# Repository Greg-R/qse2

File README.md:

QSE2DCEZ Transmitter Module

The documentation for this design is located here:
<https://kf5n.com/t41-2/qse2dcez/>

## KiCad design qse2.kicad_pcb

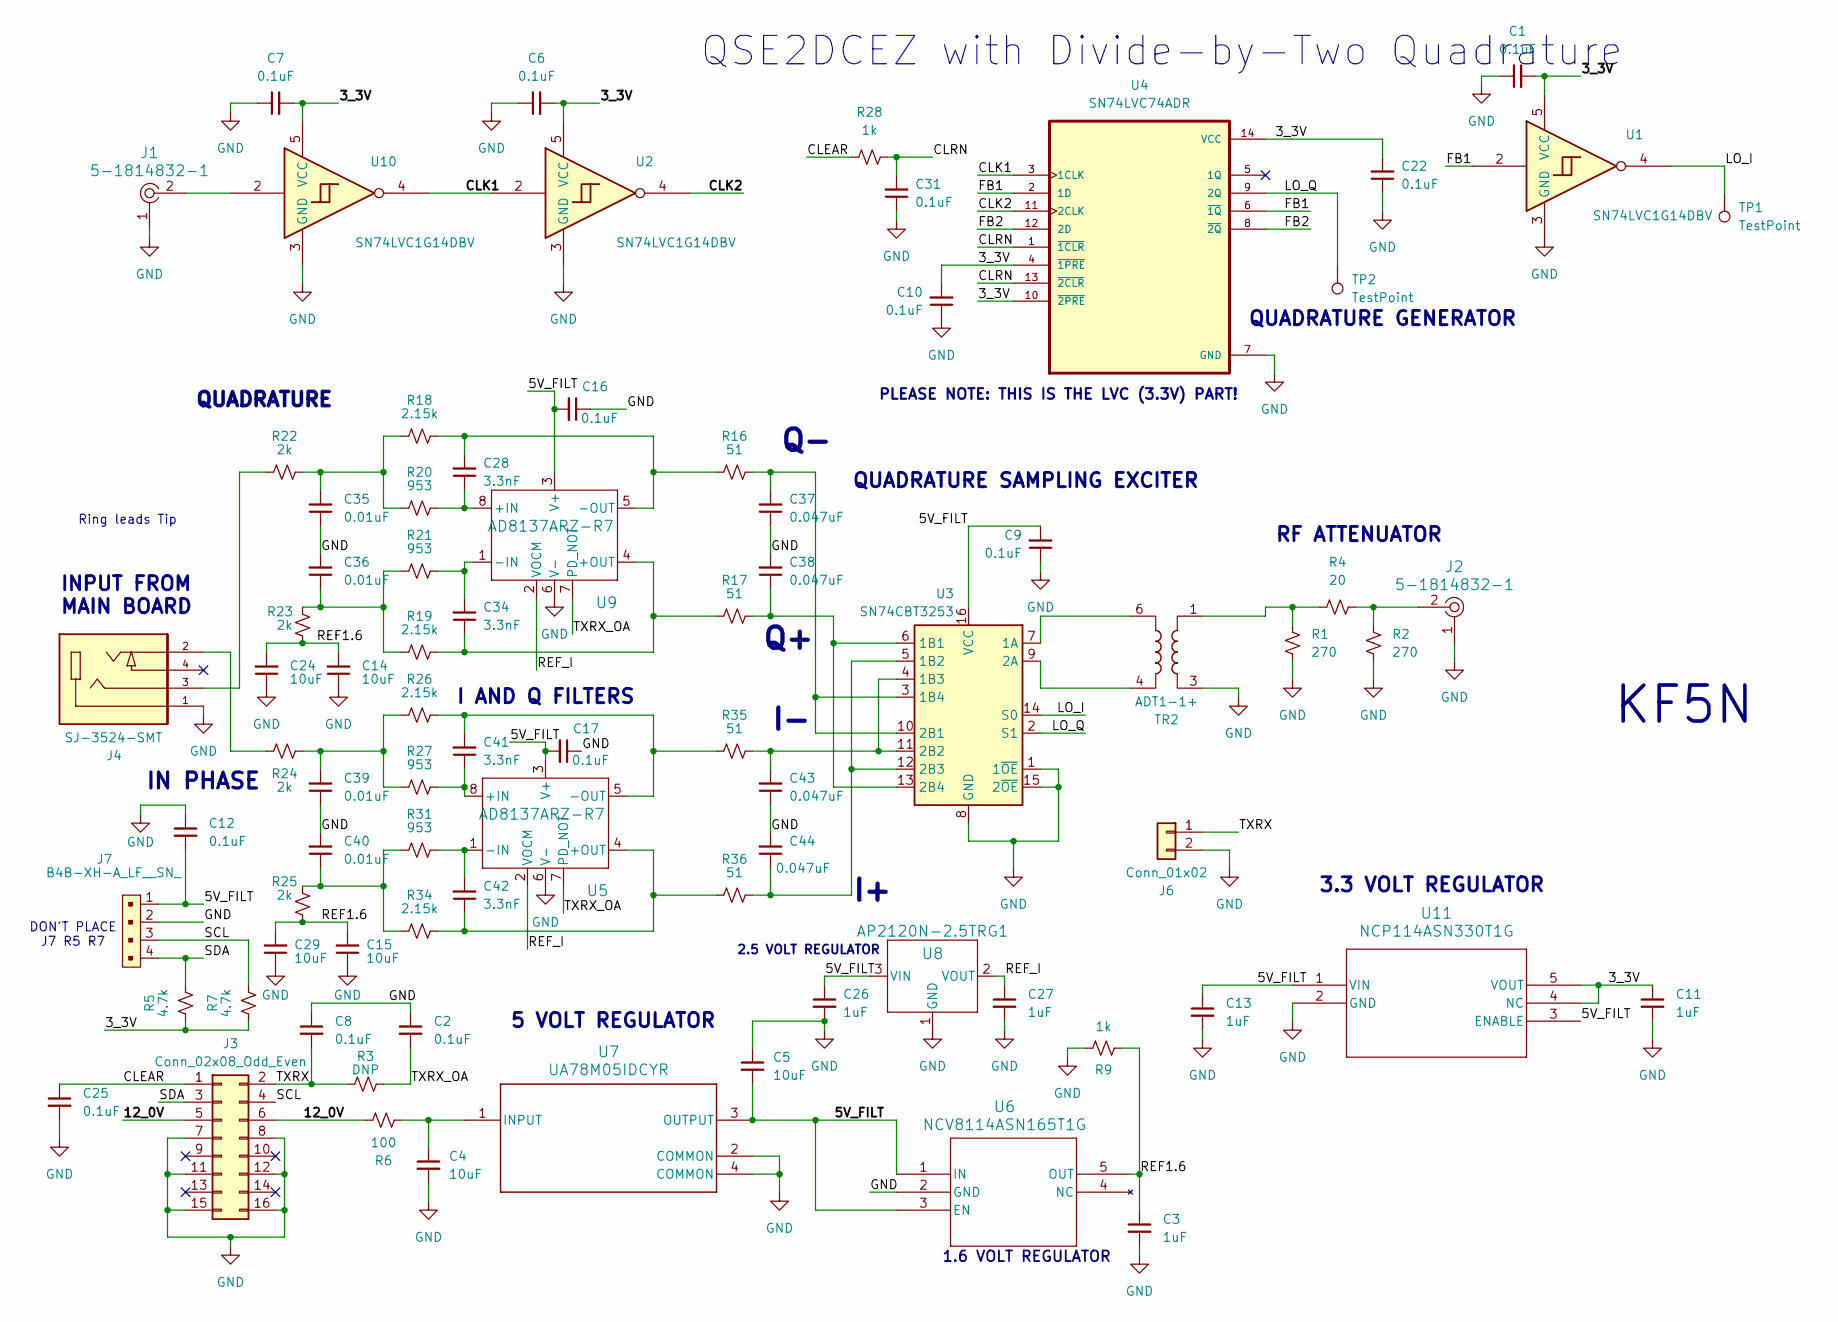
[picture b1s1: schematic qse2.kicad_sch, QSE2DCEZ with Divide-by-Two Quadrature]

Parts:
C1, C2, C6, C7, C8, C9, C10, C12, C16, C17, C22, C25, C31: 0.1uF; C_1206_3216Metric
C3, C11, C13, C26, C27: 1uF; C_1206_3216Metric
C4, C5, C14, C15, C24, C29: 10uF; C_1206_3216Metric
C28, C34, C41, C42: 3.3nF; C_1206_3216Metric
C35, C36, C39, C40: 0.01uF; C_1206_3216Metric
C37, C38, C43, C44: 0.047uF; C_1206_3216Metric
J1, J2: 5-1814832-1; RF_SMA_Vertical_5-1814832-1; MPN 5-1814832-1; Digi-Key_PN A97594-ND
J3: Conn_02x08_Odd_Even; IDC-Header_2x08_P2.54mm_Vertical
J4: SJ-3524-SMT; CUI_SJ-3524-SMT; PARTREV 1.03
J6: Conn_01x02; PinHeader_1x2_P2.5mm_Drill1.1mm
J7: B4B-XH-A_LF__SN_; PinHeader_1x4_P2.5mm_Drill1.1mm; MPN B4B-XH-A(LF)(SN); Digi-Key_PN 455-2249-ND
R1, R2: 270; R_1206_3216Metric
R3: DNP; R_1206_3216Metric
R4: 20; R_1206_3216Metric
R5, R7: 4.7k; R_1206_3216Metric
R6: 100; R_1206_3216Metric
R9, R28: 1k; R_1206_3216Metric
R16, R17, R35, R36: 51; R_1206_3216Metric
R18, R19, R26, R34: 2.15k; R_1206_3216Metric
R20, R21, R27, R31: 953; R_1206_3216Metric
R22, R23, R24, R25: 2k; R_1206_3216Metric
TP1, TP2: TestPoint; TestPoint_Pad_D1.0mm
TR2: ADT1-1+; Mini-Circuits_CD542_H2.84mm
U1, U2, U10: SN74LVC1G14DBV; SOT-23-5
U3: SN74CBT3253; SOIC-16_3.9x9.9mm_P1.27mm
U4: SN74LVC74ADR; SOIC-14_3.9x8.7mm_P1.27mm
U5, U9: AD8137ARZ-R7; R_8_ADI
U6: NCV8114ASN165T1G; TSOP-5-483-N_ONS
U7: UA78M05IDCYR; DCY0004A_N
U8: AP2120N-2.5TRG1; SOT-23_DIO
U11: NCP114ASN330T1G; TSOP-5-483-N_ONS

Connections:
/3_3V: C1.2, C6.2, C7.2, C10.2, C11.1, C22.2, R5.1, R7.1, U1.5 (VCC), U2.5 (VCC), U4.4 (~1PRE), U4.10 (~2PRE), U4.14 (VCC), U10.5 (VCC), U11.4 (NC), U11.5 (VOUT)
/5V_FILT: C5.2, C9.2, C12.2, C13.1, C16.2, C17.2, C26.1, J7.1, U3.16 (VCC), U5.3 (V+), U6.1 (IN), U6.3 (EN), U7.3 (OUTPUT), U8.3 (VIN), U9.3 (V+), U11.1 (VIN), U11.3 (ENABLE)
/12_0V: J3.5, J3.6, R6.1
/CLEAR: C25.1, J3.1, R28.1
/CLK1: U2.2, U4.3 (1CLK), U10.4
/CLK2: U2.4, U4.11 (2CLK)
/CLRN: C31.2, R28.2, U4.1 (~1CLR), U4.13 (~2CLR)
/FB1: U1.2, U4.2 (1D), U4.6 (~1Q)
/FB2: U4.8 (~2Q), U4.12 (2D)
/LO_I: TP1.1 (1_1), U1.4, U3.14 (S0)
/LO_Q: TP2.1 (1_1), U3.2 (S1), U4.9 (2Q)
/REF1.6: C3.1, C14.2, C15.2, C24.2, C29.2, R9.2, R23.1, R25.1, U6.5 (OUT)
/REF_I: C27.1, U5.2 (VOCM), U8.2 (VOUT), U9.2 (VOCM)
/SCL: J3.4, J7.3, R7.2
/SDA: J3.3, J7.4, R5.2
/TXRX: C8.2, J3.2, J6.1, R3.1
/TXRX_OA: C2.2, R3.2, U5.7 (PD_NOT), U9.7 (PD_NOT)
GND: C1.1, C2.1, C3.2, C4.2, C5.1, C6.1, C7.1, C8.1, C9.1, C10.1, C11.2, C12.1, C13.2, C14.1, C15.1, C16.1, C17.1, C22.1, C24.1, C25.2, C26.2, C27.2, C29.1, C31.1, C35.1, C36.2, C37.1, C38.2, C39.1, C40.2, C43.1, C44.2, J1.1, J2.1, J3.7, J3.8, J3.11, J3.12, J3.15, J3.16, J4.1, J6.2, J7.2, R1.2, R2.2, R9.1, TR2.3, U1.3 (GND), U2.3 (GND), U3.1 (1~OE), U3.8 (GND), U3.15 (2~OE), U4.7 (GND), U5.6 (V-), U6.2 (GND), U7.2 (COMMON), U7.4 (COMMON), U8.1 (GND), U9.6 (V-), U10.3 (GND), U11.2 (GND)
unnamed: C35.2, R18.1, R20.1, R22.2
unnamed: C36.1, R19.1, R21.1, R23.2
unnamed: C39.2, R24.2, R26.1, R27.1
unnamed: C40.1, R25.2, R31.1, R34.1
unnamed: J1.2, U10.2
unnamed: J2.2, R2.1, R4.2
unnamed: J4.2, R24.1
unnamed: J4.3, R22.1
unnamed: R1.1, R4.1, TR2.1
unnamed: TR2.6, U3.7 (1A)
unnamed: C38.1, R17.2, U3.6 (1B1), U3.13 (2B4)
unnamed: C44.1, R36.2, U3.5 (1B2), U3.12 (2B3)
unnamed: C43.2, R35.2, U3.4 (1B3), U3.11 (2B2)
unnamed: C37.2, R16.2, U3.3 (1B4), U3.10 (2B1)
unnamed: TR2.4, U3.9 (2A)
unnamed: C41.1, R27.2, U5.8 (+IN)
unnamed: C42.1, R34.2, R36.1, U5.4 (+OUT)
unnamed: C42.2, R31.2, U5.1 (-IN)
unnamed: C41.2, R26.2, R35.1, U5.5 (-OUT)
unnamed: C4.1, R6.2, U7.1 (INPUT)
unnamed: C28.1, R20.2, U9.8 (+IN)
unnamed: C34.1, R17.1, R19.2, U9.4 (+OUT)
unnamed: C34.2, R21.2, U9.1 (-IN)
unnamed: C28.2, R16.1, R18.2, U9.5 (-OUT)

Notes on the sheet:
Ring leads Tip
3.3 VOLT REGULATOR
KF5N
QUADRATURE
DON'T PLACE J7 R5 R7
IN PHASE
QUADRATURE SAMPLING EXCITER
QUADRATURE GENERATOR
1.6 VOLT REGULATOR
RF ATTENUATOR
PLEASE NOTE: THIS IS THE LVC (3.3V) PART!
INPUT FROM MAIN BOARD
I AND Q FILTERS
5 VOLT REGULATOR
QSE2DCEZ with Divide-by-Two Quadrature
2.5 VOLT REGULATOR

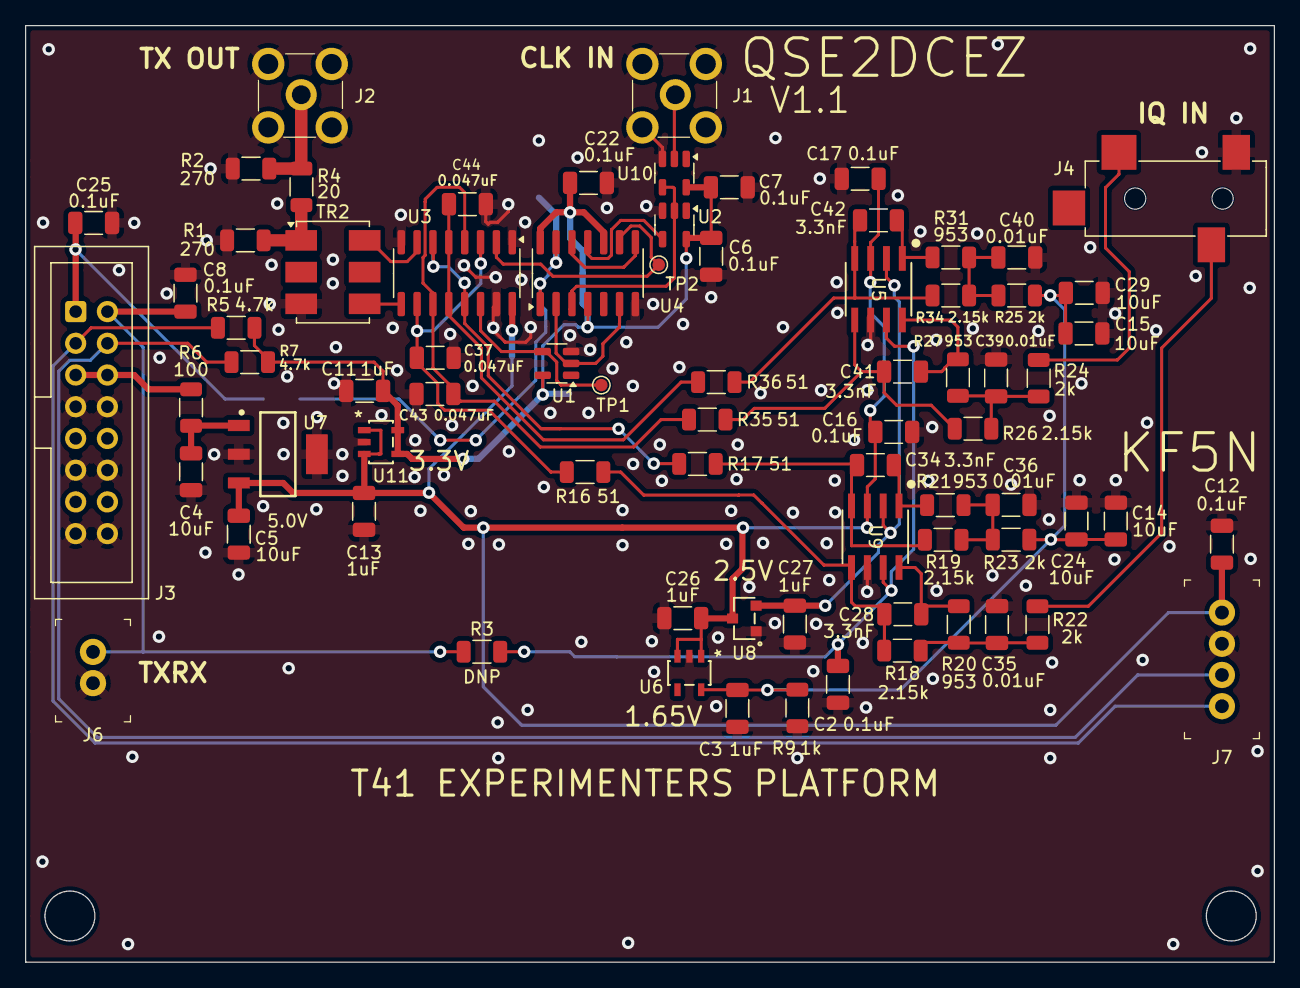
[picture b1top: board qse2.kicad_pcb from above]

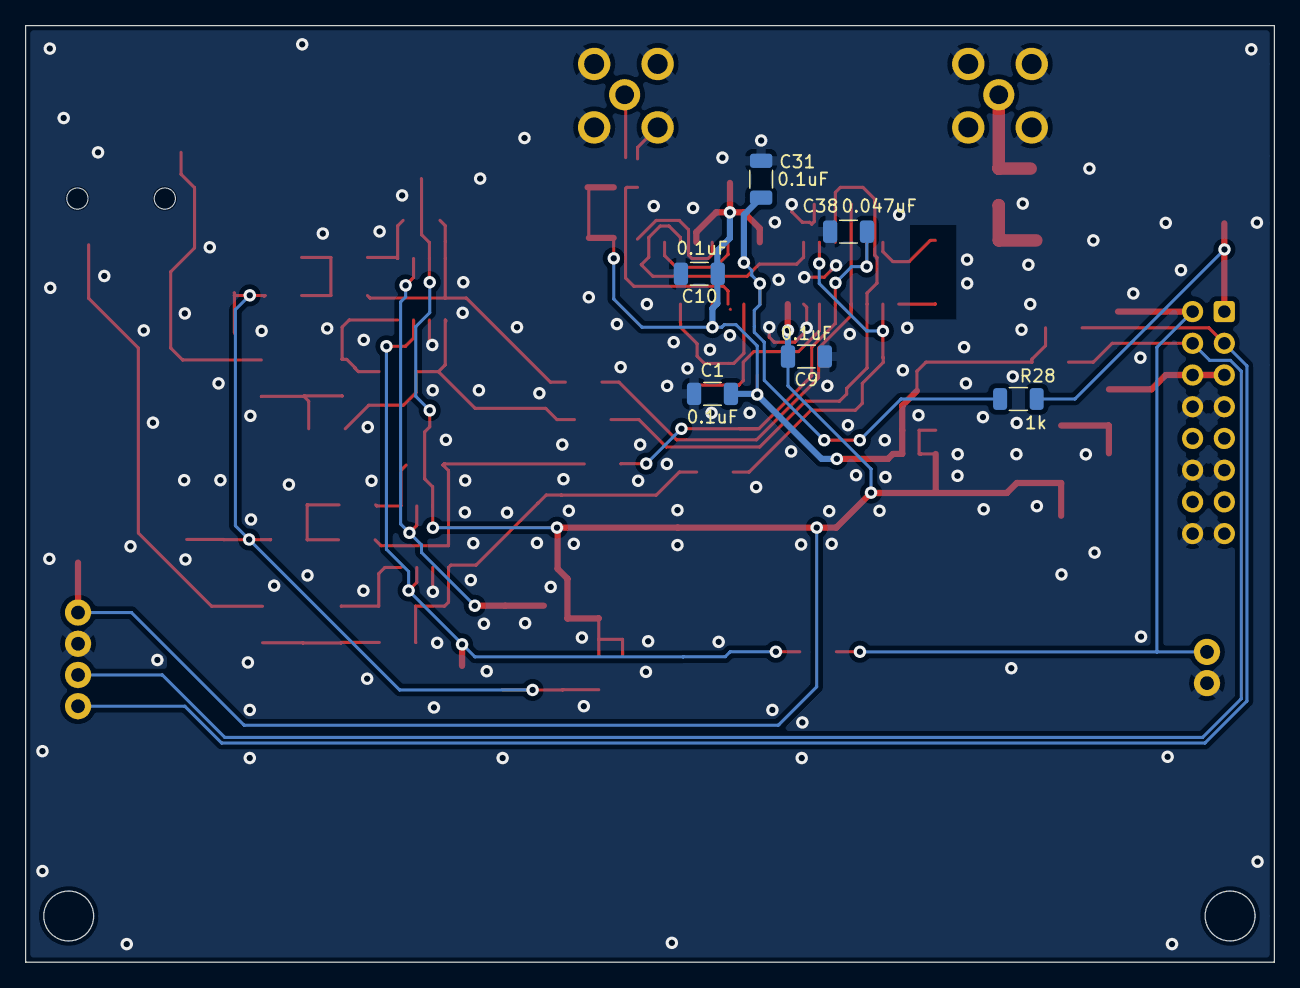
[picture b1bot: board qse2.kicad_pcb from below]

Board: 2 copper layers, 100.0 x 75.0 mm, 81 parts (6 on the bottom side), 42 nets.

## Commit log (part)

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2024-03-05 Initial commit.
2024-03-05 Cleaned up gerbers.
2024-03-05 Removed obsolete backup directories.
2024-03-05 Another obsolete directory removed.
2024-03-05 Updated schematic PDF.
2024-03-06 README.md ready to publish.
2024-03-06 Added blockquotes to code chunks in README.md.
2024-03-06 Blockquotes replaced with tabs for code in README.md.
2024-03-14 Minor change to schematic text.
2024-03-16 Added description of Audio Adapter changes to README.md.
2024-03-16 Updated README with comment about old QSE boards still working with revised Audio Adapter.
2024-03-28 Minor update to front silkscreen.
2024-04-22 Updated link to book in README.
2024-06-17 Minor revision of Gerbers.
2024-06-17 Announcement of revision in progress.
2024-06-26 Final gerbers before June release to PCB.
2024-06-29 Mostly cleaned up version with SOICs replacing TSOPs.
2024-07-01 Ready to release V1.1 June 30.
2024-07-26 Released to fab.
2024-07-26 Revised README for Version 1.1 QSE2DC with improved quadrature.
2024-07-26 Minor edit to README.
2024-07-26 Minor change to README.
2024-07-26 Updated README and very minor update to Gerbers.
2024-07-26 Minor fix to README.
2024-07-26 Updated README.
2024-07-27 Added notes to schematic.
2024-07-27 Backups updated.
2024-07-27 Updated note on README about non-placed parts.
2024-07-27 Updated note on README.
2024-08-19 Fixed regulator part numbers on schematic.
2024-10-14 Release to fab.
2026-03-11 Clean up and update to new version Kicad.
2026-05-20 Swapped SDA and SCL to correct pins.
